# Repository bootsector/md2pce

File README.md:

# MD2PCE - Sega Genesis controller adapter for TG16/PC-Engine and USB!
(c) Bruno Freitas - 10/2020 - http://www.brunofreitas.com/

This project is Open Source (GPLv3) and Open Hardware (CC BY-SA 4.0)

MD2PCE is an adapter that allows you to connect Sega Genesis controllers to the TurboGrafx16, PC-Engine and also PC via USB (XInput).

It's compatible with both 3 and 6 buttons Sega Genesis controllers. It also supports the 8BitDo M30 2.4g with its wireless DB9 receiver.

MD2PCE Adapter starts in 2 button mode, which ensures 100% compatibility with all PCE/TG16 games catalog. For games supporting 6 button controllers, you can switch to 6 button mode, and also switching back to 2 button mode, by pressing the combo keys: UP + B + C + Start.

Mappings for both 2 and 6 button modes are:

The adapter needs male-male 8 pin DIN (TG16) or Mini-DIN (PCE) cables that must be purchased separately.

For using on PC via USB, you'll need a mini-USB cable that also must be purchased separately.

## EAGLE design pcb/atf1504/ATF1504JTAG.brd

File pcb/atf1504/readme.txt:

This shield is based on https://github.com/hackup/ATF2FT232HQ

If CPLD is used and it needs JTAG erasing, connect a 12V PSU and run (OpenOCD version 0.10.0-rc2):

bin-x64\openocd.exe -f scripts\interface\ftdi\um232h.cfg -c "adapter_khz 400" -c "transport select jtag" -c "jtag newtap ATF1504AS tap -irlen 3 -expected-id 0x0150403f" -c init -c "svf atf1504as-erase.svf" -c "sleep 200" -c shutdown

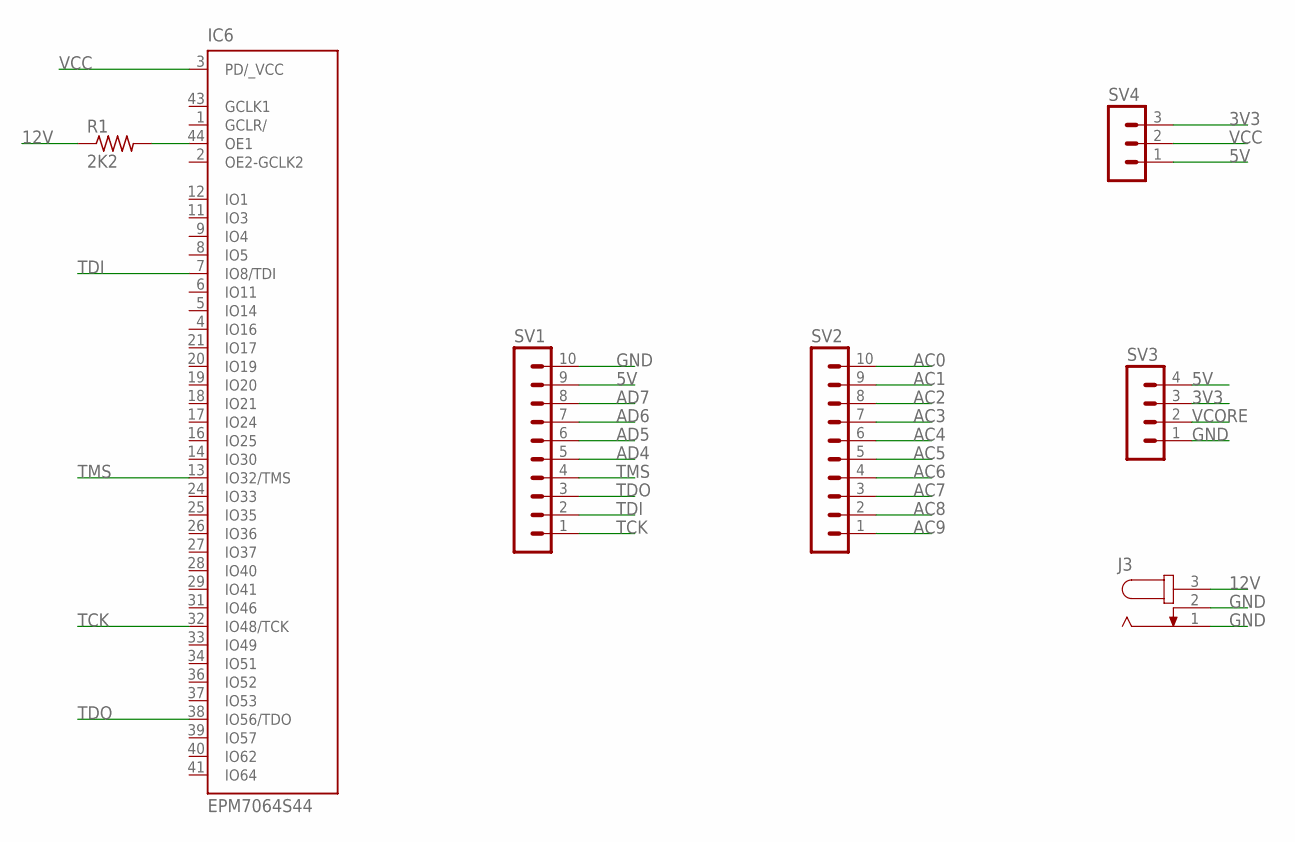
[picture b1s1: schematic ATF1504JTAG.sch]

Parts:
IC6: EPM7064S44; PLCC-S44
J3: JACK-PLUG1; SPC4078
R1: 2K2; 0207/10
SV1, SV2: MA10-1
SV3: MA04-1
SV4: MA03-1

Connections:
3V3: SV3.3, SV4.3
5V: SV1.9, SV3.4, SV4.1
12V: J3.3, R1.1
AC0: SV2.10
AC1: SV2.9
AC2: SV2.8
AC3: SV2.7
AC4: SV2.6
AC5: SV2.5
AC6: SV2.4
AC7: SV2.3
AC8: SV2.2
AC9: SV2.1
AD4: SV1.5
AD5: SV1.6
AD6: SV1.7
AD7: SV1.8
GND: IC6.10 (GND), IC6.22 (GND), IC6.30 (GND), IC6.42 (GND), J3.1, J3.2, SV1.10, SV3.1
unnamed: IC6.44 (OE1), R1.2
TCK: IC6.32 (IO48/TCK), SV1.1
TDI: IC6.7 (IO8/TDI), SV1.2
TDO: IC6.38 (IO56/TDO), SV1.3
TMS: IC6.13 (IO32/TMS), SV1.4
VCC: IC6.3 (PD/_VCC), IC6.15 (VCC), IC6.23 (VCC), IC6.35 (VCC), SV4.2
VCORE: SV3.2

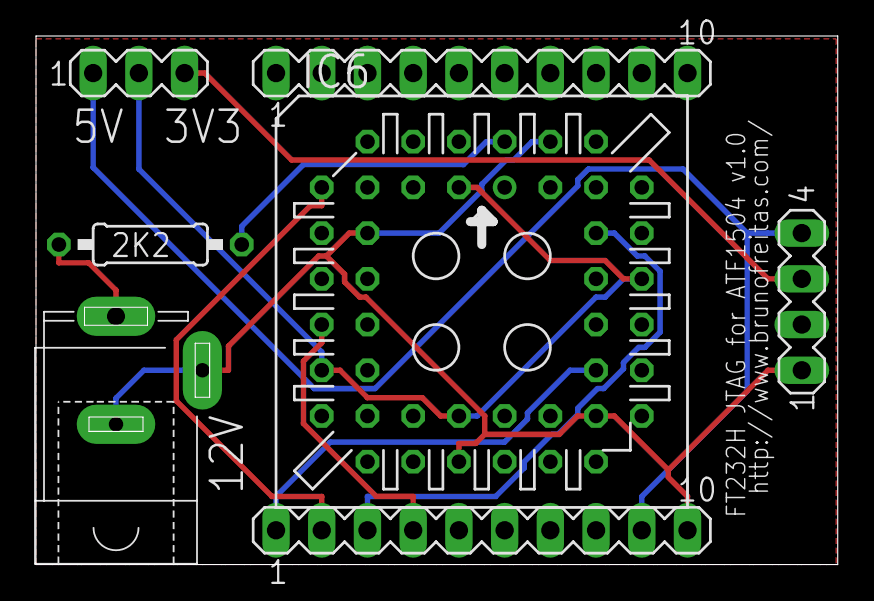
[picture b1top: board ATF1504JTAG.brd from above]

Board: 2 copper layers, 44.5 x 29.4 mm, 7 parts (0 on the bottom side), 10 nets.

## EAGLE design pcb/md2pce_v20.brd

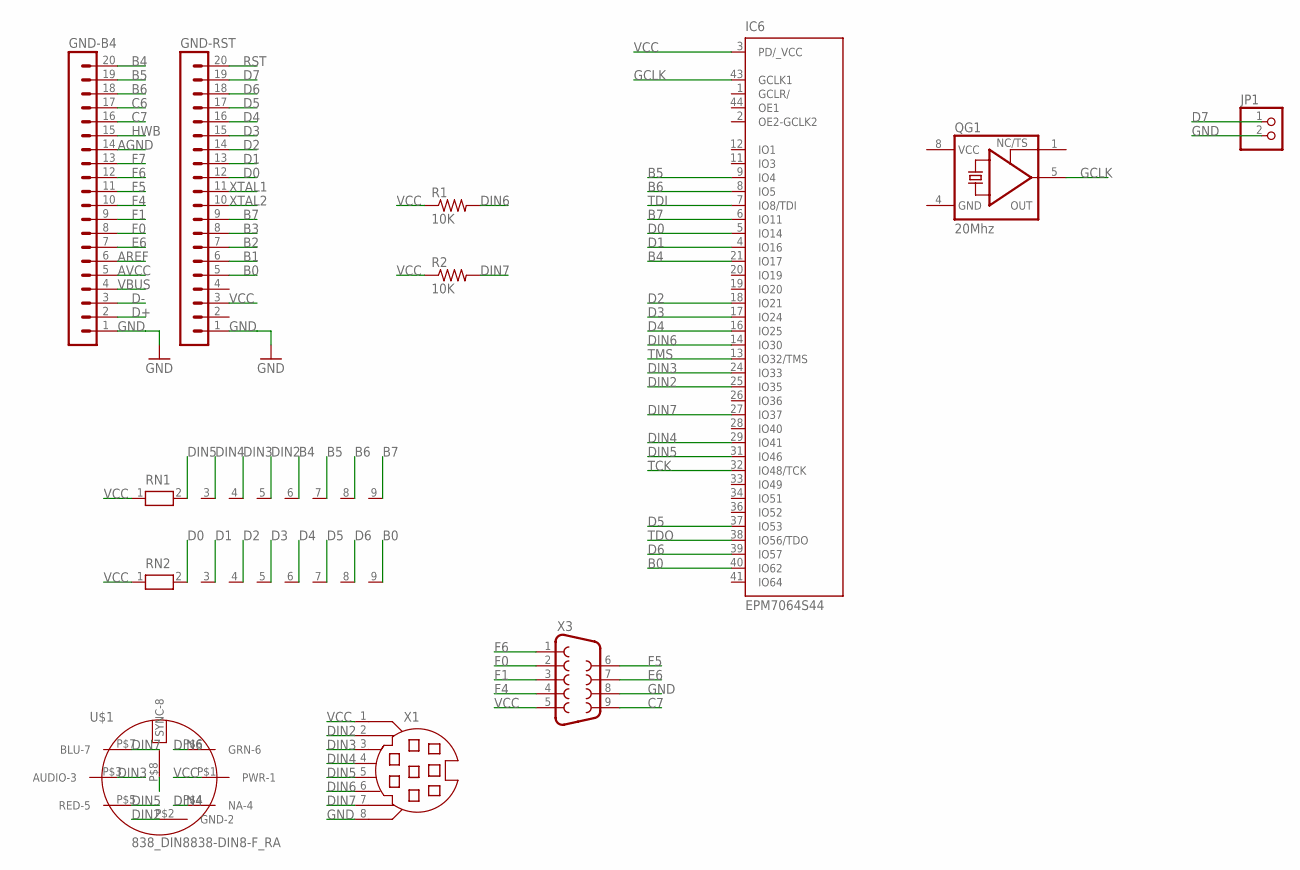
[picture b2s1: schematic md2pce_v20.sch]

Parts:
GND-B4: MA20-1
GND-RST: MA20-1
IC6: EPM7064S44; PLCC-S44
JP1: PINHD-1X2; 1X02
QG1: 20Mhz; DIL08S
R1, R2: 10K; 0207/10
RN1, RN2: RN08; RN-9
U$1: 838_DIN8838-DIN8-F_RA; 838_DIN8
X1: MD08SS; MDIN08SS
X3: DB9MALE; DB9_MALE

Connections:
AGND: GND-B4.14
AREF: GND-B4.6
AVCC: GND-B4.5
B0: GND-RST.5, IC6.40 (IO62), RN2.9
B1: GND-RST.6
B2: GND-RST.7
B3: GND-RST.8
B4: GND-B4.20, IC6.21 (IO17), RN1.6
B5: GND-B4.19, IC6.9 (IO4), RN1.7
B6: GND-B4.18, IC6.8 (IO5), RN1.8
B7: GND-RST.9, IC6.6 (IO11), RN1.9
C6: GND-B4.17
C7: GND-B4.16, X3.9
D0: GND-RST.12, IC6.5 (IO14), RN2.2
D1: GND-RST.13, IC6.4 (IO16), RN2.3
D2: GND-RST.14, IC6.18 (IO21), RN2.4
D3: GND-RST.15, IC6.17 (IO24), RN2.5
D4: GND-RST.16, IC6.16 (IO25), RN2.6
D5: GND-RST.17, IC6.37 (IO53), RN2.7
D6: GND-RST.18, IC6.39 (IO57), RN2.8
D7: GND-RST.19, JP1.1
D+: GND-B4.2
D-: GND-B4.3
DIN2: IC6.25 (IO35), RN1.5, U$1.P$2 (GND-2), X1.2
DIN3: IC6.24 (IO33), RN1.4, U$1.P$3 (AUDIO-3), X1.3
DIN4: IC6.29 (IO41), RN1.3, U$1.P$4 (NA-4), X1.4
DIN5: IC6.31 (IO46), RN1.2, U$1.P$5 (RED-5), X1.5
DIN6: IC6.14 (IO30), R1.2, U$1.P$6 (GRN-6), X1.6
DIN7: IC6.27 (IO37), R2.2, U$1.P$7 (BLU-7), X1.7
E6: GND-B4.7, X3.7
F0: GND-B4.8, X3.2
F1: GND-B4.9, X3.3
F4: GND-B4.10, X3.4
F5: GND-B4.11, X3.6
F6: GND-B4.12, X3.1
F7: GND-B4.13
GCLK: IC6.43 (GCLK1), QG1.5 (OUT)
GND: GND-B4.1, GND-RST.1, IC6.10 (GND), IC6.22 (GND), IC6.30 (GND), IC6.42 (GND), JP1.2, QG1.4 (GND), U$1.P$8 (SYNC-8), X1.8, X3.8
HWB: GND-B4.15
RST: GND-RST.20
TCK: IC6.32 (IO48/TCK)
TDI: IC6.7 (IO8/TDI)
TDO: IC6.38 (IO56/TDO)
TMS: IC6.13 (IO32/TMS)
VBUS: GND-B4.4
VCC: GND-RST.3, IC6.3 (PD/_VCC), IC6.15 (VCC), IC6.23 (VCC), IC6.35 (VCC), QG1.8 (VCC), R1.1, R2.1, RN1.1, RN2.1, U$1.P$1 (PWR-1), X1.1, X3.5
XTAL1: GND-RST.11
XTAL2: GND-RST.10

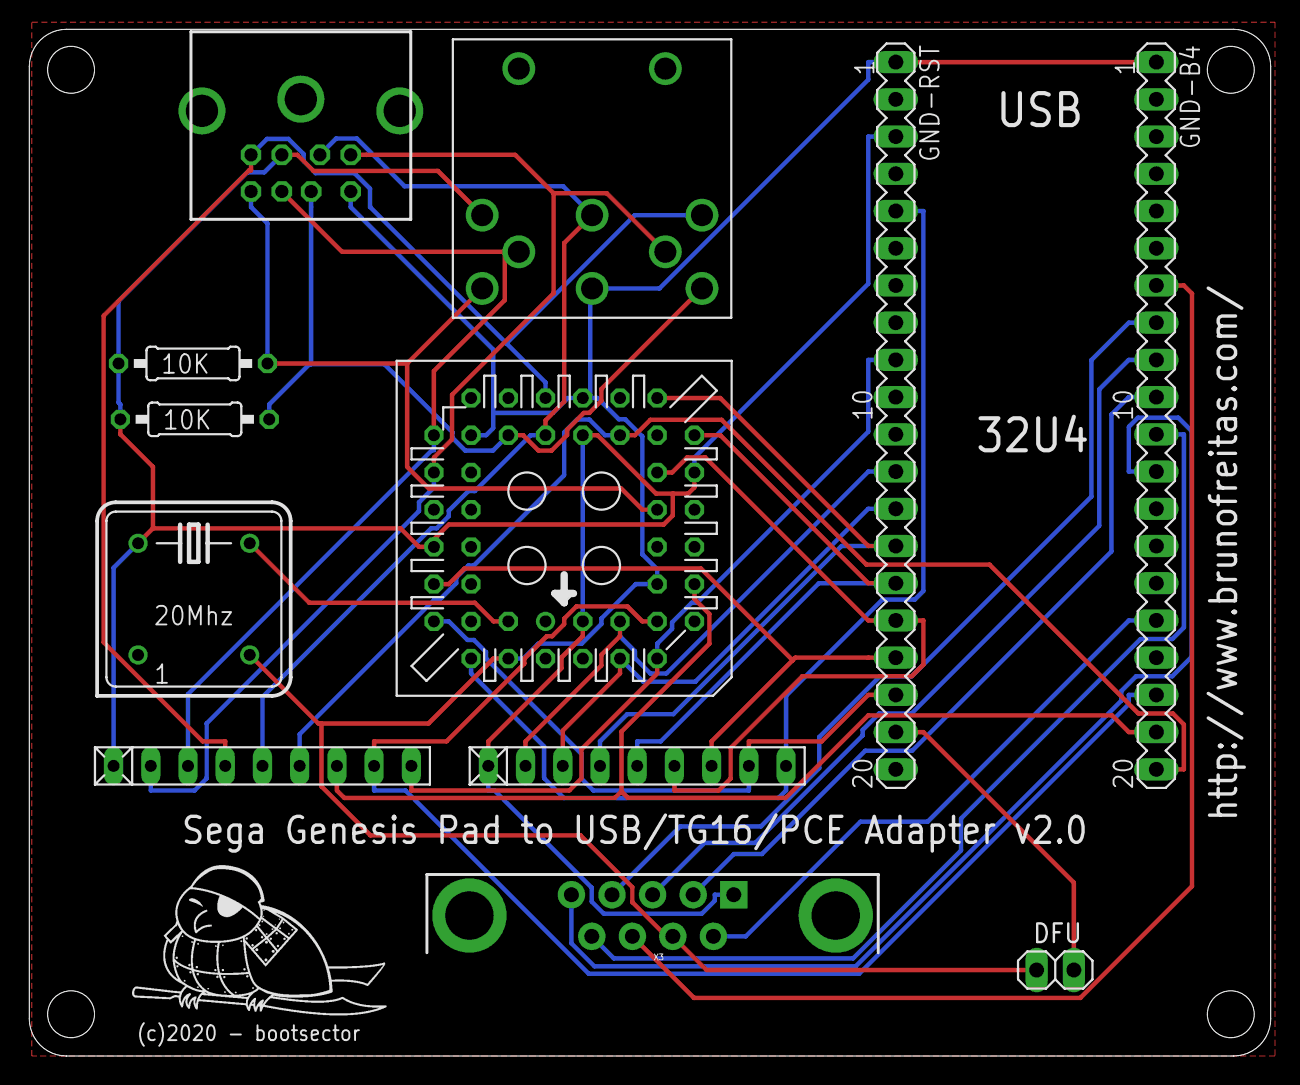
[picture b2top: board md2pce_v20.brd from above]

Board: 2 copper layers, 84.7 x 70.1 mm, 12 parts (0 on the bottom side), 29 nets.

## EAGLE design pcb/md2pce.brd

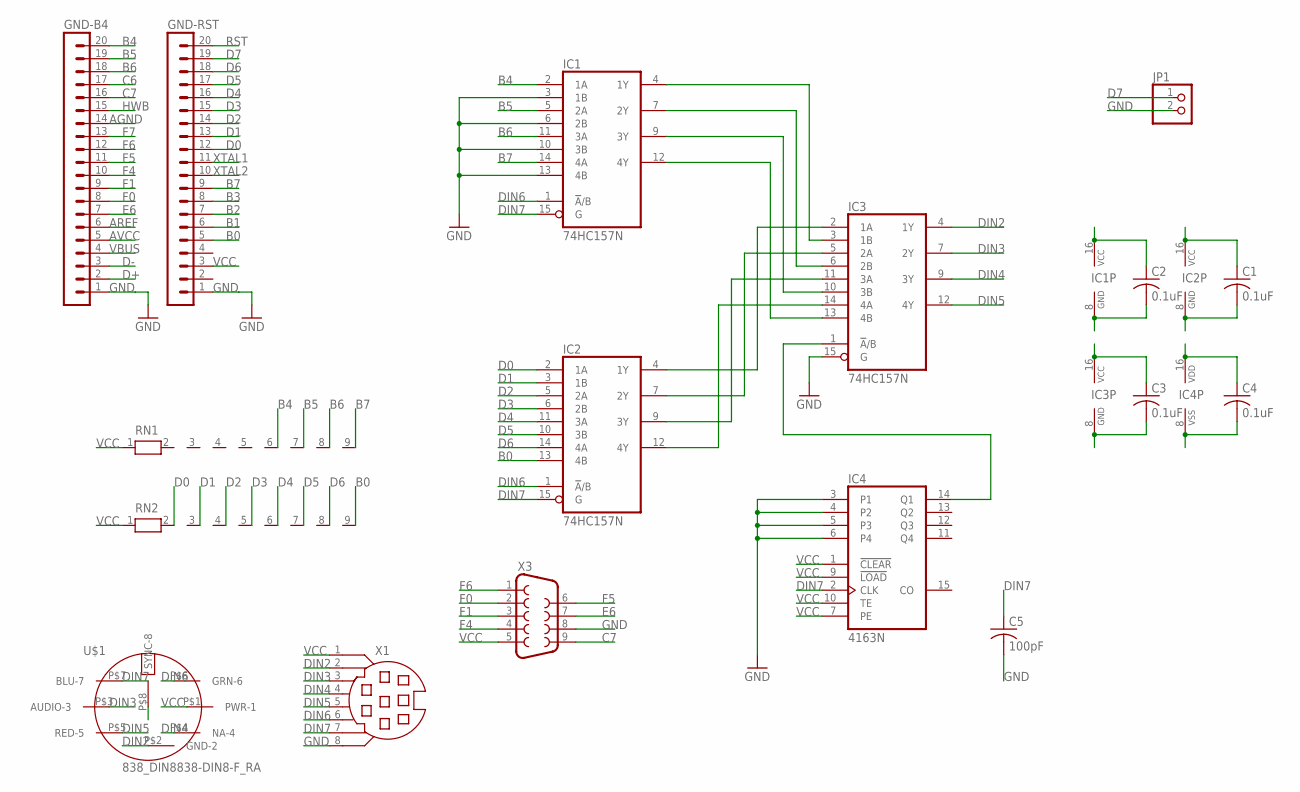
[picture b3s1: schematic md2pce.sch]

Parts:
C1, C2, C3, C4: 0.1uF; C025-024X044
C5: 100pF; C025-024X044
GND-B4: MA20-1
GND-RST: MA20-1
IC1, IC2, IC3: 74HC157N; DIL16
IC4: 4163N; DIL16
JP1: PINHD-1X2; 1X02
RN1, RN2: RN08; RN-9
U$1: 838_DIN8838-DIN8-F_RA; 838_DIN8
X1: MD08SS; MDIN08SS
X3: DB9MALE; DB9_MALE

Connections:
AGND: GND-B4.14
AREF: GND-B4.6
AVCC: GND-B4.5
B0: GND-RST.5, IC2.13 (4B), RN2.9
B1: GND-RST.6
B2: GND-RST.7
B3: GND-RST.8
B4: GND-B4.20, IC1.2 (1A), RN1.6
B5: GND-B4.19, IC1.5 (2A), RN1.7
B6: GND-B4.18, IC1.11 (3A), RN1.8
B7: GND-RST.9, IC1.14 (4A), RN1.9
C6: GND-B4.17
C7: GND-B4.16, X3.9
D0: GND-RST.12, IC2.2 (1A), RN2.2
D1: GND-RST.13, IC2.3 (1B), RN2.3
D2: GND-RST.14, IC2.5 (2A), RN2.4
D3: GND-RST.15, IC2.6 (2B), RN2.5
D4: GND-RST.16, IC2.11 (3A), RN2.6
D5: GND-RST.17, IC2.10 (3B), RN2.7
D6: GND-RST.18, IC2.14 (4A), RN2.8
D7: GND-RST.19, JP1.1
D+: GND-B4.2
D-: GND-B4.3
DIN2: IC3.4 (1Y), U$1.P$2 (GND-2), X1.2
DIN3: IC3.7 (2Y), U$1.P$3 (AUDIO-3), X1.3
DIN4: IC3.9 (3Y), U$1.P$4 (NA-4), X1.4
DIN5: IC3.12 (4Y), U$1.P$5 (RED-5), X1.5
DIN6: IC1.1 (!A!/B), IC2.1 (!A!/B), U$1.P$6 (GRN-6), X1.6
DIN7: C5.1, IC1.15 (G), IC2.15 (G), IC4.2 (CLK), U$1.P$7 (BLU-7), X1.7
E6: GND-B4.7, X3.7
F0: GND-B4.8, X3.2
F1: GND-B4.9, X3.3
F4: GND-B4.10, X3.4
F5: GND-B4.11, X3.6
F6: GND-B4.12, X3.1
F7: GND-B4.13
GND: C1.2, C2.2, C3.2, C4.2, C5.2, GND-B4.1, GND-RST.1, IC1.3 (1B), IC1.6 (2B), IC1.8 (GND), IC1.10 (3B), IC1.13 (4B), IC2.8 (GND), IC3.8 (GND), IC3.15 (G), IC4.3 (P1), IC4.4 (P2), IC4.5 (P3), IC4.6 (P4), IC4.8 (VSS), JP1.2, U$1.P$8 (SYNC-8), X1.8, X3.8
HWB: GND-B4.15
unnamed: IC1.4 (1Y), IC3.3 (1B)
unnamed: IC1.7 (2Y), IC3.6 (2B)
unnamed: IC1.9 (3Y), IC3.10 (3B)
unnamed: IC1.12 (4Y), IC3.13 (4B)
unnamed: IC2.4 (1Y), IC3.2 (1A)
unnamed: IC2.7 (2Y), IC3.5 (2A)
unnamed: IC2.9 (3Y), IC3.11 (3A)
unnamed: IC2.12 (4Y), IC3.14 (4A)
unnamed: IC3.1 (!A!/B), IC4.14 (Q1)
RST: GND-RST.20
VBUS: GND-B4.4
VCC: C1.1, C2.1, C3.1, C4.1, GND-RST.3, IC1.16 (VCC), IC2.16 (VCC), IC3.16 (VCC), IC4.1 (!CLEAR), IC4.7 (PE), IC4.9 (!LOAD), IC4.10 (TE), IC4.16 (VDD), RN1.1, RN2.1, U$1.P$1 (PWR-1), X1.1, X3.5
XTAL1: GND-RST.11
XTAL2: GND-RST.10

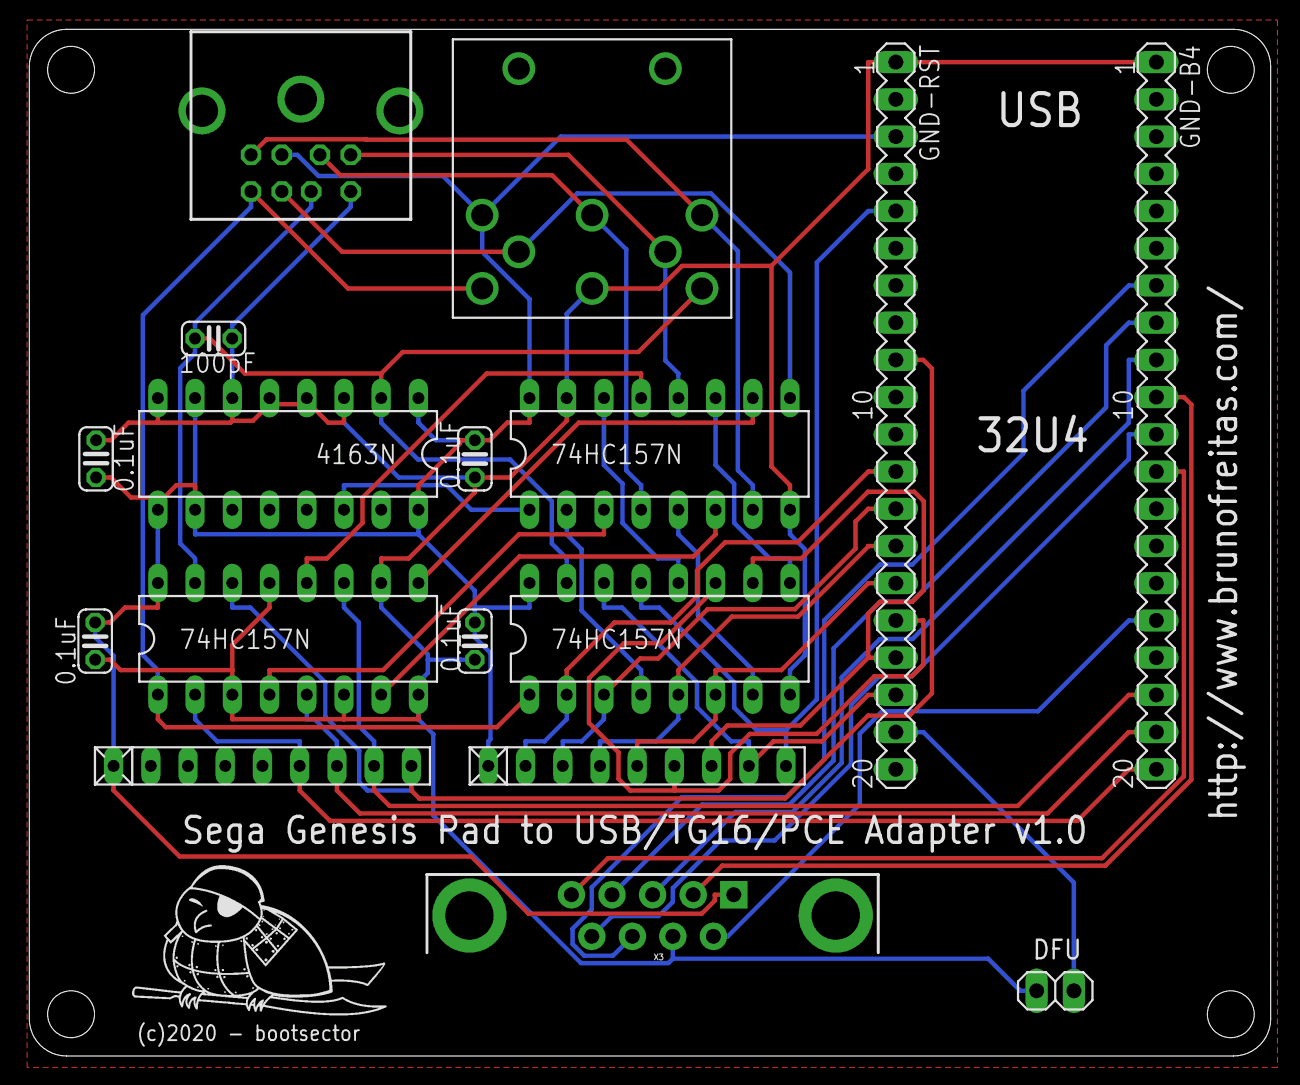
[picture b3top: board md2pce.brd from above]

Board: 2 copper layers, 84.7 x 70.1 mm, 17 parts (0 on the bottom side), 37 nets.

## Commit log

2020-07-03 Added firmware sources
2020-07-03 Adding acrylic case designs
2020-07-04 Adding .gitignore
2020-07-04 Added vscode workspace file
2020-07-05 VSCode workspace re-structure
2020-07-05 PCE output improvements
2020-07-06 Fixing temp variables type
2020-07-07 Do not use USB watchdog so it does not get rebooted on the TG16 and PCE
2020-08-07 Start working on verilog module for a PCE 6 button encoder
2020-08-07 PCE verilog encoder WIP
2020-08-07 .gitignore update
2020-08-08 PCB version 2.0 (using CPLD). Added Quartus project files.
2020-08-13 Added gerber for an Atmel ATF1504 JTAG programmer shield for cheap FT232 module
2020-08-14 Added ATF1504 JTAG shield readme and blank SVF files for JTAG erasing, if necessary.
2020-09-09 Adding 1ms timer
2020-09-09 Adding debounce logic when reading Sega Genesis pad
2020-09-09 Improves 1ms timer against jitter
2020-09-09 Removed overall debounce logic and improved Genesis 6 button required delay logic
2020-09-09 500us delay looks enough for a 6 button controller settling between reads.
2020-10-04 Improved reading of sega genesis 6 button controller - removed 500us busy delay
2020-10-04 Revert "Improved reading of sega genesis 6 button controller - removed 500us busy delay"
    This reverts commit 2b43a497c3b5f5f0b78716028848ced92a060647.
2020-10-08 Corrected inverted bits in Verilog PCE encoder. Hyperkin six button controller needs bigger delay between reads.
2020-10-09 Added combo for switching between 2 and 6 button mode output (thanks @brNX). Mapping A to SELECT for 3 button sega genesis controllers
2020-10-13 Improved compatibility with six button hyperkin controllers
2020-10-15 Adding README
2020-10-15 Fix image paths inside README
2020-10-15 Added Atmega 32u4 board schematics and gerber files
2020-10-15 Adding bootloader sources
2020-10-15 Add licensing info to the README
2021-06-07 Adding svf file for ATF1504AS
2022-09-20 Enabled Reduce MC Power for ATF1504 in SVF

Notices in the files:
pcb/md2pce.brd:
(c)2020 - bootsector
